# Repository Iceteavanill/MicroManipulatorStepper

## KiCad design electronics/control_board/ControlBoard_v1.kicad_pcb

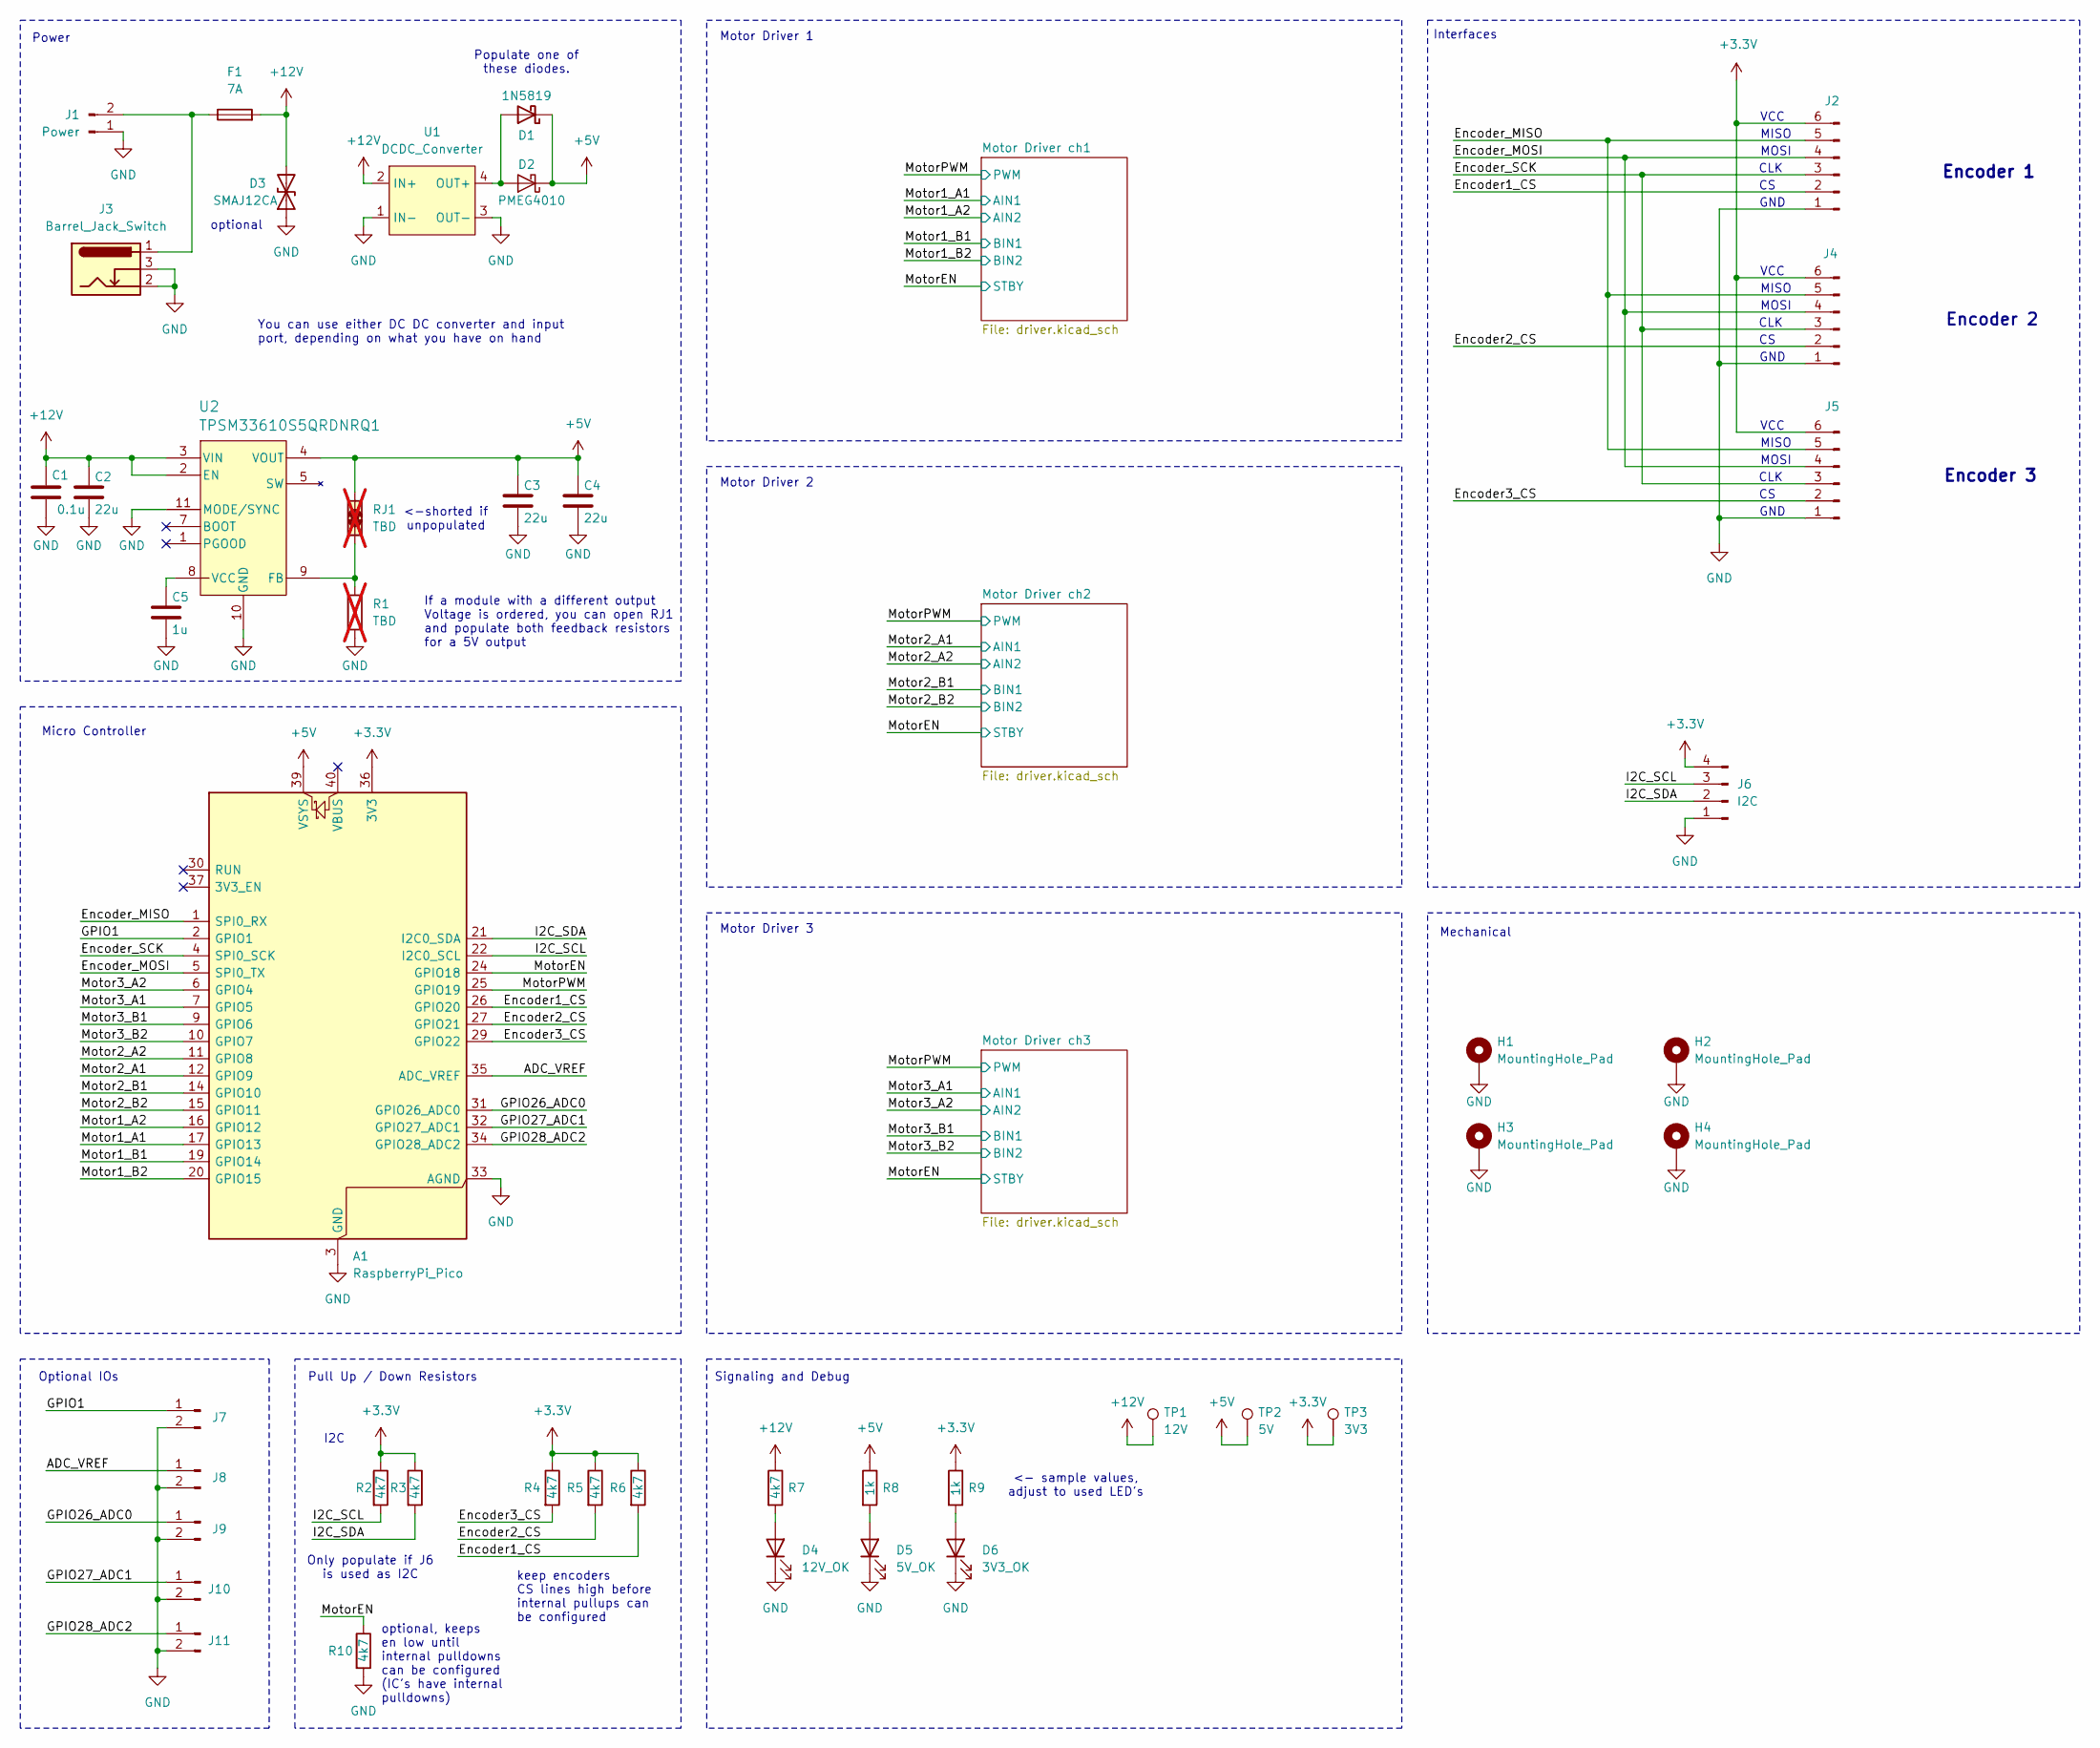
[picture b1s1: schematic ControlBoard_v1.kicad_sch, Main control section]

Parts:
A1: RaspberryPi_Pico; RaspberryPi_Pico_Common_Unspecified
C1: 0.1u; C_0603_1608Metric_Pad1.08x0.95mm_HandSolder
C2, C3, C4: 22u; C_0805_2012Metric_Pad1.18x1.45mm_HandSolder
C5: 1u; C_0805_2012Metric_Pad1.18x1.45mm_HandSolder
D1: 1N5819; D_DO-41_SOD81_P10.16mm_Horizontal
D2: PMEG4010; D_SOD-123F
D3: SMAJ12CA; D_SMA_Handsoldering
D4: 12V_OK; LED_0805_2012Metric_Pad1.15x1.40mm_HandSolder
D5: 5V_OK; LED_0805_2012Metric_Pad1.15x1.40mm_HandSolder
D6: 3V3_OK; LED_0805_2012Metric_Pad1.15x1.40mm_HandSolder
F1: 7A; Fuse_1206_3216Metric_Pad1.42x1.75mm_HandSolder
H1, H2, H3, H4: MountingHole_Pad; MountingHole_2.7mm_M2.5_Pad_Via
J1: Power; AMASS_XT60-M_1x02_P7.20mm_Vertical
J2, J4, J5: Conn_01x06_Pin; JST_PH_B6B-PH-K_1x06_P2.00mm_Vertical
J3: Barrel_Jack_Switch; BarrelJack_Horizontal
J6: I2C; JST_PH_B4B-PH-K_1x04_P2.00mm_Vertical
J7, J8, J9, J10, J11: Conn_01x02_Pin; PinHeader_1x02_P2.54mm_Vertical
R1: TBD; R_0603_1608Metric_Pad0.98x0.95mm_HandSolder; not fitted
R2, R3, R4, R5, R6, R7, R10: 4k7; R_0603_1608Metric_Pad0.98x0.95mm_HandSolder
R8, R9: 1k; R_0603_1608Metric_Pad0.98x0.95mm_HandSolder
RJ1: TBD; 0603_shorted_resistor; not fitted
TP1: 12V; TestPoint_Pad_D2.0mm
TP2: 5V; TestPoint_Pad_D2.0mm
TP3: 3V3; TestPoint_Pad_D2.0mm
U1: DCDC_Converter; DCDC_17mmx12mm
U2: TPSM33610S5QRDNRQ1

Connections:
+3.3V: A1.36 (3V3), J2.6, J4.6, J5.6, J6.4, R2.1, R3.1, R4.1, R5.1, R6.1, R9.1, TP3.1 (1_1); also elsewhere on the board
+5V: A1.39 (VSYS), C3.1, C4.1, D1.1 (K), D2.1 (K), R8.1, RJ1.1, TP2.1 (1_1), U2.4 (VOUT)
+12V: C1.1, C2.1, D3.2 (A2), F1.2, R7.1, TP1.1 (1_1), U1.2 (IN+), U2.2 (EN), U2.3 (VIN); also elsewhere on the board
/ADC_VREF: A1.35 (ADC_VREF), J8.1
/Encoder1_CS: A1.26 (GPIO20), J2.2, R6.2
/Encoder2_CS: A1.27 (GPIO21), J4.2, R5.2
/Encoder3_CS: A1.29 (GPIO22), J5.2, R4.2
/Encoder_MISO: A1.1 (SPI0_RX), J2.5, J4.5, J5.5
/Encoder_MOSI: A1.5 (SPI0_TX), J2.4, J4.4, J5.4
/Encoder_SCK: A1.4 (SPI0_SCK), J2.3, J4.3, J5.3
/GPIO1: A1.2 (GPIO1), J7.1
/GPIO26_ADC0: A1.31 (GPIO26_ADC0), J9.1
/GPIO27_ADC1: A1.32 (GPIO27_ADC1), J10.1
/GPIO28_ADC2: A1.34 (GPIO28_ADC2), J11.1
/I2C_SCL: A1.22 (I2C0_SCL), J6.3, R2.2
/I2C_SDA: A1.21 (I2C0_SDA), J6.2, R3.2
/Motor1_A1: A1.17 (GPIO13); also elsewhere on the board
/Motor1_A2: A1.16 (GPIO12); also elsewhere on the board
/Motor1_B1: A1.19 (GPIO14); also elsewhere on the board
/Motor1_B2: A1.20 (GPIO15); also elsewhere on the board
/Motor2_A1: A1.12 (GPIO9); also elsewhere on the board
/Motor2_A2: A1.11 (GPIO8); also elsewhere on the board
/Motor2_B1: A1.14 (GPIO10); also elsewhere on the board
/Motor2_B2: A1.15 (GPIO11); also elsewhere on the board
/Motor3_A1: A1.7 (GPIO5); also elsewhere on the board
/Motor3_A2: A1.6 (GPIO4); also elsewhere on the board
/Motor3_B1: A1.9 (GPIO6); also elsewhere on the board
/Motor3_B2: A1.10 (GPIO7); also elsewhere on the board
/MotorEN: A1.24 (GPIO18), R10.1; also elsewhere on the board
/MotorPWM: A1.25 (GPIO19); also elsewhere on the board
GND: A1.3 (GND), A1.8 (GND), A1.13 (GND), A1.18 (GND), A1.23 (GND), A1.28 (GND), A1.33 (AGND), A1.38 (GND), C1.2, C2.2, C3.2, C4.2, C5.2, D3.1 (A1), D4.1 (K), D5.1 (K), D6.1 (K), H1.1 (1_1), H2.1 (1_1), H3.1 (1_1), H4.1 (1_1), J1.1, J2.1, J3.2, J3.3, J4.1, J5.1, J6.1, J7.2, J8.2, J9.2, J10.2, J11.2, R1.2, R10.2, U1.1 (IN-), U1.3 (OUT-), U2.10 (GND), U2.11 (MODE/SYNC); also elsewhere on the board
unnamed: D1.2 (A), D2.2 (A), U1.4 (OUT+)
unnamed: D4.2 (A), R7.2
unnamed: D5.2 (A), R8.2
unnamed: D6.2 (A), R9.2
unnamed: F1.1, J1.2, J3.1
unnamed: R1.1, RJ1.2, U2.9 (FB)
unnamed: C5.1, U2.8 (VCC)

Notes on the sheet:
<- sample values, adjust to used LED's
Only populate if J6 is used as I2C
Encoder 2
<-shorted if unpopulated
keep encoders CS lines high before internal pullups can be configured
Encoder 3
Optional IOs
If a module with a different output Voltage is ordered, you can open RJ1 and populate both feedback resistors for a 5V output
MOSI
Power
MISO
VCC
GND
Motor Driver 2
CLK
optional, keeps en low until internal pulldowns can be configured (IC's have internal pulldowns)
You can use either DC DC converter and input port, depending on what you have on hand
Interfaces
Motor Driver 1
I2C
Encoder 1
optional
Pull Up / Down Resistors
Mechanical
Motor Driver 3
Populate one of these diodes.
Signaling and Debug
Micro Controller

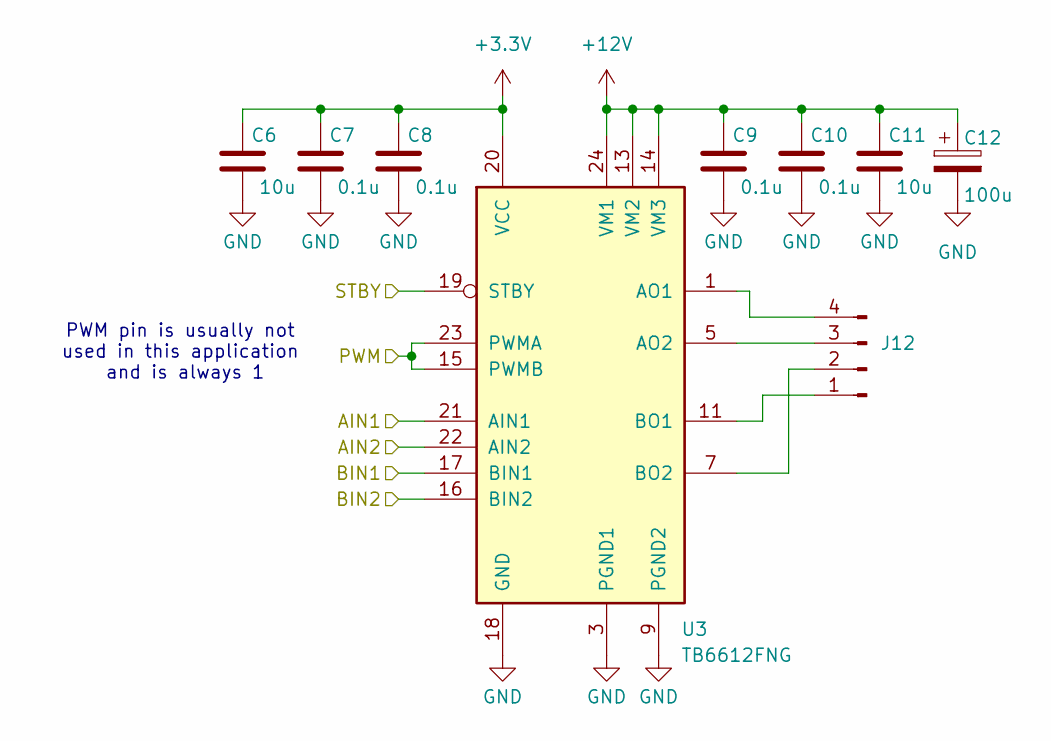
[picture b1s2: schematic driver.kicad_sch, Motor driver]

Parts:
C6, C11: 10u; C_0805_2012Metric_Pad1.18x1.45mm_HandSolder
C7, C8, C9, C10: 0.1u; C_0603_1608Metric_Pad1.08x0.95mm_HandSolder
C12: 100u; CP_Radial_D6.3mm_P2.50mm
J12: PinHeader_1x04_P2.54mm_Vertical
U3: TB6612FNG; SSOP-24_5.3x8.2mm_P0.65mm

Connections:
+3.3V: C6.1, C7.1, C8.1, U3.20 (VCC); also elsewhere on the board
+12V: C9.1, C10.1, C11.1, C12.1, U3.13 (VM2), U3.14 (VM3), U3.24 (VM1); also elsewhere on the board
/Motor1_A1: U3.21 (AIN1); also elsewhere on the board
/Motor1_A2: U3.22 (AIN2); also elsewhere on the board
/Motor1_B1: U3.17 (BIN1); also elsewhere on the board
/Motor1_B2: U3.16 (BIN2); also elsewhere on the board
/MotorEN: U3.19 (STBY); also elsewhere on the board
/MotorPWM: U3.15 (PWMB), U3.23 (PWMA); also elsewhere on the board
GND: C6.2, C7.2, C8.2, C9.2, C10.2, C11.2, C12.2, U3.3 (PGND1), U3.4 (PGND1), U3.9 (PGND2), U3.10 (PGND2), U3.18 (GND); also elsewhere on the board
unnamed: J12.1, U3.11 (BO1), U3.12 (BO1)
unnamed: J12.2, U3.7 (BO2), U3.8 (BO2)
unnamed: J12.3, U3.5 (AO2), U3.6 (AO2)
unnamed: J12.4, U3.1 (AO1), U3.2 (AO1)

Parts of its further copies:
C13, C18, C20, C25: 10u; C_0805_2012Metric_Pad1.18x1.45mm_HandSolder
C14, C15, C16, C17, C21, C22, C23, C24: 0.1u; C_0603_1608Metric_Pad1.08x0.95mm_HandSolder
C19, C26: 100u; CP_Radial_D6.3mm_P2.50mm
U4, U5: TB6612FNG; SSOP-24_5.3x8.2mm_P0.65mm

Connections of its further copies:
+3.3V: C13.1, C14.1, C15.1, C20.1, C21.1, C22.1, U4.20 (VCC), U5.20 (VCC); also elsewhere on the board
+12V: C16.1, C17.1, C18.1, C19.1, C23.1, C24.1, C25.1, C26.1, U4.13 (VM2), U4.14 (VM3), U4.24 (VM1), U5.13 (VM2), U5.14 (VM3), U5.24 (VM1); also elsewhere on the board
/Motor2_A1: U4.21 (AIN1); also elsewhere on the board
/Motor2_A2: U4.22 (AIN2); also elsewhere on the board
/Motor2_B1: U4.17 (BIN1); also elsewhere on the board
/Motor2_B2: U4.16 (BIN2); also elsewhere on the board
/Motor3_A1: U5.21 (AIN1); also elsewhere on the board
/Motor3_A2: U5.22 (AIN2); also elsewhere on the board
/Motor3_B1: U5.17 (BIN1); also elsewhere on the board
/Motor3_B2: U5.16 (BIN2); also elsewhere on the board
/MotorEN: U4.19 (STBY), U5.19 (STBY); also elsewhere on the board
/MotorPWM: U4.15 (PWMB), U4.23 (PWMA), U5.15 (PWMB), U5.23 (PWMA); also elsewhere on the board
GND: C13.2, C14.2, C15.2, C16.2, C17.2, C18.2, C19.2, C20.2, C21.2, C22.2, C23.2, C24.2, C25.2, C26.2, U4.3 (PGND1), U4.4 (PGND1), U4.9 (PGND2), U4.10 (PGND2), U4.18 (GND), U5.3 (PGND1), U5.4 (PGND1), U5.9 (PGND2), U5.10 (PGND2), U5.18 (GND); also elsewhere on the board
unnamed 40: U4.11 (BO1), U4.12 (BO1); also elsewhere on the board
unnamed 41: U4.7 (BO2), U4.8 (BO2); also elsewhere on the board
unnamed 42: U4.5 (AO2), U4.6 (AO2); also elsewhere on the board
unnamed 43: U4.1 (AO1), U4.2 (AO1); also elsewhere on the board
unnamed 44: U5.11 (BO1), U5.12 (BO1); also elsewhere on the board
unnamed 45: U5.7 (BO2), U5.8 (BO2); also elsewhere on the board
unnamed 46: U5.5 (AO2), U5.6 (AO2); also elsewhere on the board
unnamed 47: U5.1 (AO1), U5.2 (AO1); also elsewhere on the board

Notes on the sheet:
PWM pin is usually not used in this application and is always 1

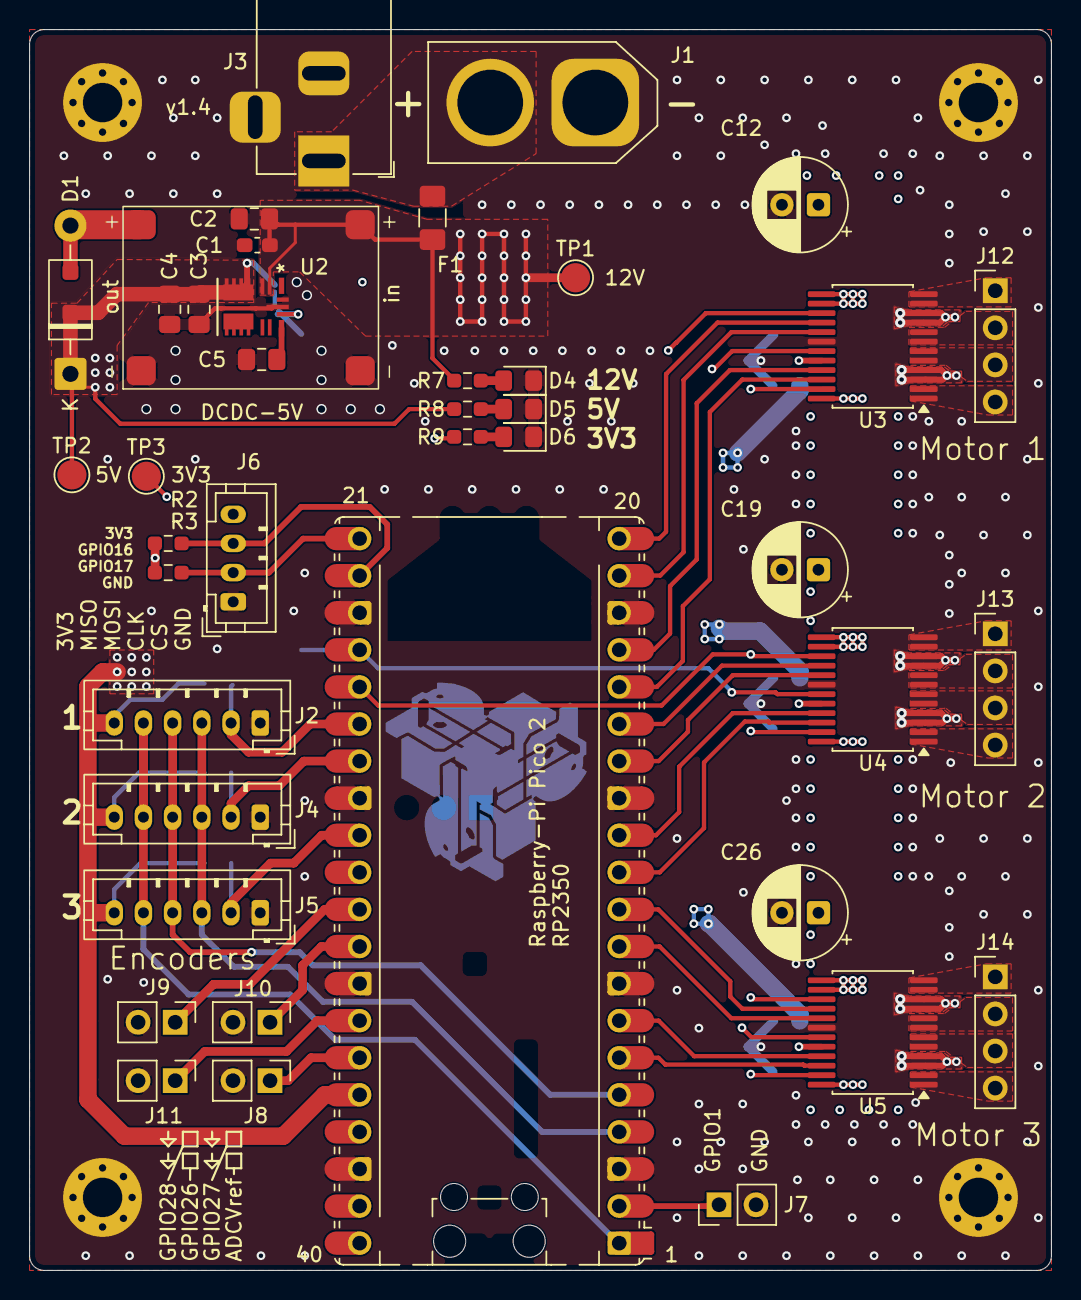
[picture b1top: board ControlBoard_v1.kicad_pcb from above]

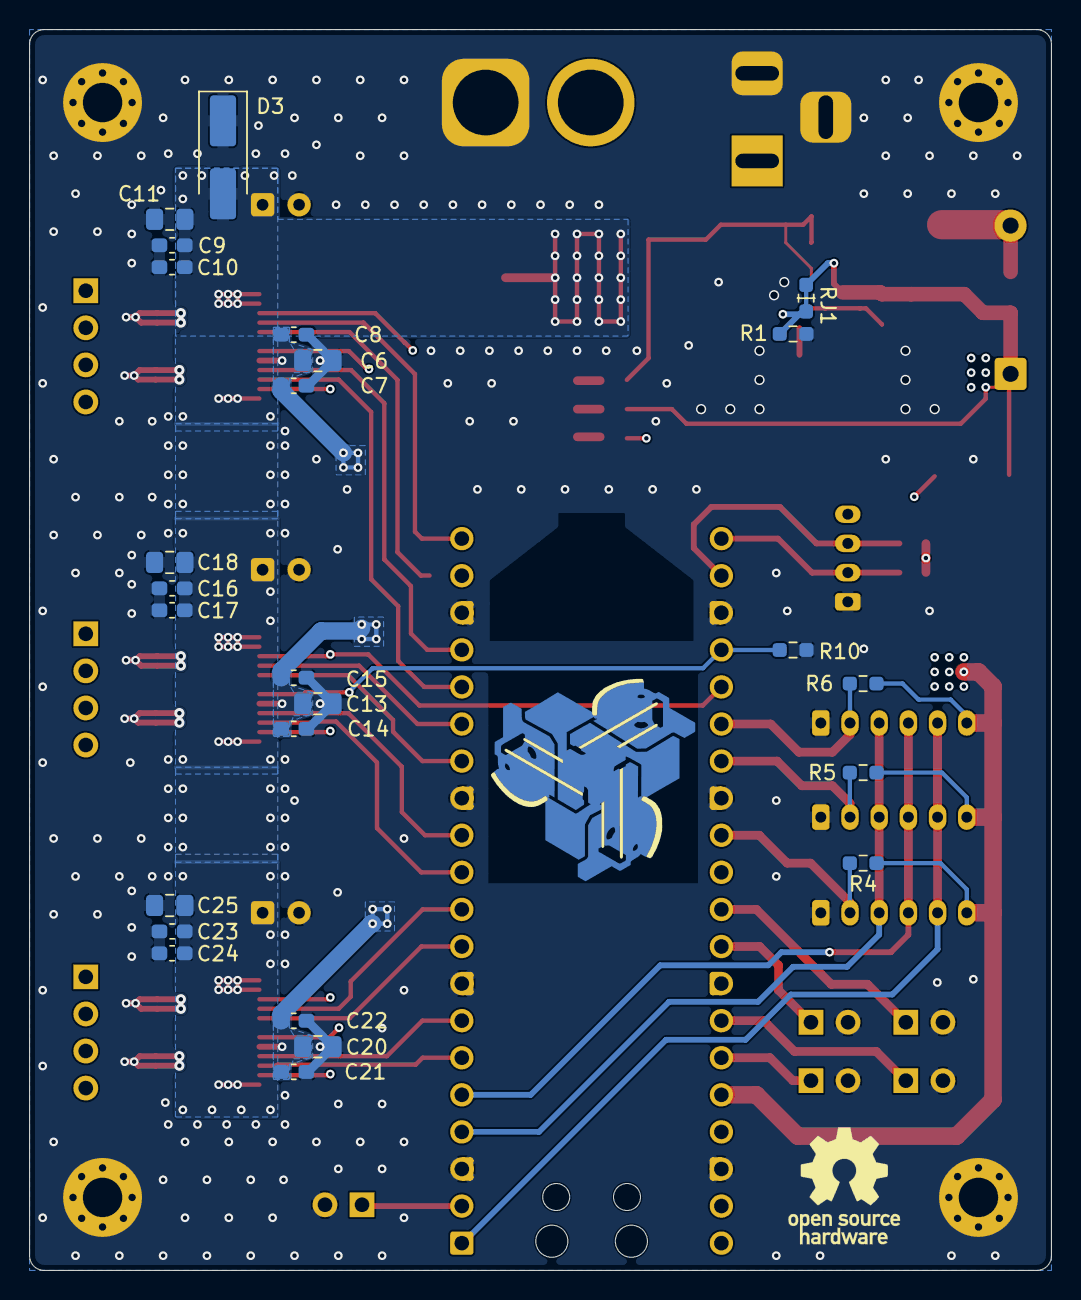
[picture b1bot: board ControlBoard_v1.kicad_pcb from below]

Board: 4 copper layers, 70.0 x 85.0 mm, 71 parts (26 on the bottom side), 50 nets.

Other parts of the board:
J13, J14: PinHeader_1x04_P2.54mm_Vertical

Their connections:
unnamed 40: J13.1; also elsewhere on the board
unnamed 41: J13.2; also elsewhere on the board
unnamed 42: J13.3; also elsewhere on the board
unnamed 43: J13.4; also elsewhere on the board
unnamed 44: J14.1; also elsewhere on the board
unnamed 45: J14.2; also elsewhere on the board
unnamed 46: J14.3; also elsewhere on the board
unnamed 47: J14.4; also elsewhere on the board

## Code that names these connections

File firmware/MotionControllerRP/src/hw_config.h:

#pragma once
#include "utilities/math_constants.h"

// #define DEMO_MODE

//--- MOTORS ------------------------------------------------------------------

// motor pole pair count
//  * 100 for 0.9deg stepper motors
//  * 50  for 1.8deg stepper motors
constexpr float MOTOR1_POLE_PAIRS = 50;
constexpr float MOTOR2_POLE_PAIRS = 50;
constexpr float MOTOR3_POLE_PAIRS = 50;

// max current factor in range [0..1]. Lower values reduce pwm resolution so a
// value above 0.4 is recommended.
constexpr float MOTOR_MAX_CURRENT_FACTOR = 0.2f;

//--- ENCODERS ----------------------------------------------------------------

// Conversion factor from encoder angle (one 2pi period every two magnets) to rotor angle.
// Used when the system can not rely on calibration data being present (e.g. during homing)
constexpr float ENCODER_MAGNET_PITCH = 3.0f;    // [mm]
constexpr float ENCODER_MAGNET_RADIUS = 30.0f;  // [mm]
constexpr float ENCODER_ANGLE_TO_ROTOR_ANGLE = (ENCODER_MAGNET_PITCH*2.0f) / 
                                               (ENCODER_MAGNET_RADIUS * Constants::TWO_PI_F);
											   
// enables error checking for encoders (slow) - useful for debugging
// Note: some chips seem to return always a crc of 0 producing massiv false errors       
constexpr bool ENABLE_ENCODER_CRC = false;

//--- HOMING ------------------------------------------------------------------

constexpr float HOMING_VELOCITY   = 1.0f;        // rad per s
constexpr float HOMING_CURRENT    = 0.15f;       // range 0..1
// NOT IMPLEMENTED YET: constexpr float HOMING_FINISH_POS = 0.5f;        // in rad

//--- CALIBRATION -------------------------------------------------------------

// degrees from home position
constexpr float CALIBRATION_RANGE = 83; 

// velocity of the magnetic field during calibration (lower is more accurate)
constexpr float CALIBRATION_FIELD_VELOCITY = 20.0f; 

// size of the calibration lookup table
constexpr int ENCODER_LUT_SIZE = 256;

//--- CLOSED LOOP CONTROL -----------------------------------------------------

// position controller 
constexpr float POS_KP = 60.0f;
constexpr float POS_KI = 30000.0f;

// velocity controller
constexpr float VEL_LOWPASS_TC = 0.004f;
constexpr float VEL_KP = 0.2f;
constexpr float VEL_KI = 90.0f;

//--- KINEMATIC ---------------------------------------------------------------

// Kinematic Parameters are defined kinematic_modes/kinematic_model_delta3d.cpp

// NUM_JOINTS and NUM_TOOLS are defined in 'path_segment.h'. Note that changing
// the number of joints requires changing the kinematic model accordingly and
// also requires the initialization of the correct number of 'RobotJoint' objects
// in the Robtos init method.

//--- PINS --------------------------------------------------------------------

#define JOINT_READY_OVERRIDE

// #define SINGLE_AXIS_BOARD
#ifndef SINGLE_AXIS_BOARD
  // Pins for 3Axis Board
  // #define PIN_BUILTIN_LED 23 // RP2040 pico clone
  // #define PIN_USER_BUTTON 24 // RP2040 pico clone
  #define PIN_BUILTIN_LED 25

  #define PIN_M1_PWM_A_POS  13
  #define PIN_M1_PWM_A_NEG  12
  #define PIN_M1_PWM_B_POS  14
  #define PIN_M1_PWM_B_NEG  15

  #define PIN_M2_PWM_A_POS  9
  #define PIN_M2_PWM_A_NEG  8
  #define PIN_M2_PWM_B_POS  10
  #define PIN_M2_PWM_B_NEG  11

  #define PIN_M3_PWM_A_POS  5
  #define PIN_M3_PWM_A_NEG  4
  #define PIN_M3_PWM_B_POS  6
  #define PIN_M3_PWM_B_NEG  7


  #define PIN_MOTOR_EN      18
  #define PIN_MOTOR_PWMAB   19

  #define PIN_ENCODER1_CS 20
  #define PIN_ENCODER2_CS 21
  #define PIN_ENCODER3_CS 22
  #define PIN_ENCODER_SCK 2
  #define PIN_ENCODER_MISO 0
  #define PIN_ENCODER_MOSI 3

  #define PIN_TOOL1 16
  #define PIN_TOOL2 17

#else
  // Single Axis Board
  #define PIN_BUILTIN_LED 16
  #define PIN_USER_BUTTON 24

  #define PIN_M1_PWM_A_POS  13
  #define PIN_M1_PWM_A_NEG  12
  #define PIN_M1_PWM_B_POS  14
  #define PIN_M1_PWM_B_NEG  15

  #define PIN_M2_PWM_A_POS  9
  #define PIN_M2_PWM_A_NEG  8
  #define PIN_M2_PWM_B_POS  10
  #define PIN_M2_PWM_B_NEG  11

  #define PIN_M3_PWM_A_POS  5
  #define PIN_M3_PWM_A_NEG  4
  #define PIN_M3_PWM_B_POS  6
  #define PIN_M3_PWM_B_NEG  7


  #define PIN_MOTOR_EN      18
  #define PIN_MOTOR_PWMAB   19

  #define PIN_ENCODER1_CS 20
  #define PIN_ENCODER2_CS 21
  #define PIN_ENCODER3_CS 22
  #define PIN_ENCODER_SCK 2
  #define PIN_ENCODER_MISO 0
  #define PIN_ENCODER_MOSI 3
#endif
